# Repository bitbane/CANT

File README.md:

The CANT project is designed to allow people to screw around with CAN easily at layers 1/2.
All of the stuff that is normally handled by a CAN controller that is baked into sillicon is up for grabs.

CANT is designed to run on an ST Micro [Nucleo-H743ZI](http://www.st.com/en/evaluation-tools/nucleo-h743zi.html) 
(Update: The Nucleo-H743ZI has been discontinued. Its replacement the Nucleo-H743ZI2 works with CANT out of the box).
development board. This board was chosen due to its speed (400MHz) and essentially infinite ram and flash.

Note: If you have a MB1364C (and possibly D) revision of this board, the solder bridge at SB7 has to be soldered
closed to enable the GPIO pin. On revisions B and E this is controlled by the jumper JP6 which is in place by default.

## Getting started with the Nucleo-STM32H7 development board

The Nucleo-H743ZI board has an STLink V2.1 debugger built in, available via the Micro-USB port on the 
opposite side of the board from the RJ-45 jack. This port provides the serial port for communication, 
as well as the debugging interface. The serial port has a baud rate of 115200 kbps, 8N1. 

For CAN communication, PB12 is CAN RX and PB13 is CAN TX. Conveniently the CAN2 peripheral can also be 
multiplexed to these pins, so switching from normal CAN operation to CANT operation would be 
possible without rewiring. This is currently not implemented. I'm using the 
[TI SN65HVD232](http://www.ti.com/product/sn65hvd232?qgpn=sn65hvd232) 3.3V CAN transceiver, 
but any 3.3V CAN Transceiver should work. Some transceivers may require some additional 
programming or wiring, so check that if you go with something else.

If you are using the CANT shield, pin PA5 is used to toggle the analog switch that shorts CANH and CANL
together.

Additionally, GPIO pins PA4 and PA15 are configured as GPIO outputs. I find banging on these
useful during debugging. These pins, along with the two pins for the CAN peripheral, are all located
on connector CN7, on the upper-right of the dev board if the RJ-45 connector is pointed towards you.
STs documentation contains the schematics for this board, but connector CN7 is reproduced here for
convenience:

| PIN |     |     | PIN |
|:---:|:---:|:---:|:---:|
| PC6 | 1   | 2   | PB8 |
| PB15| 3   | 4   | PB9 |
| PB13| 5   | 6   | AVDD|
| PB12| 7   | 8   | GND |
| PA15| 9   | 10  | PA5 |
| PC7 | 11  | 12  | PA6 |
| PB5 | 13  | 14  |     |
| PB3 | 15  | 16  | PD14|
| PA4 | 17  | 18  | PD15|
| PB4 | 19  | 20  | PF12|

### Flashing pre-built CANT
The Nucleo-H743ZI dev board will present itself as a USB mass storage device. Dragging and dropping the CANT.bin file 
located in the `firmware/` folder to the dev board should properly flash the code to the dev board.

Alternatively, you will need openocd installed to flash the prebuilt CANT. At the time of this writing the latest version
of openocd (0.10.0) does not support the H743ZI, but it is supported in the openocd git repository.
Presumably support will be added in the next release of openocd. In order to flash the prebuilt CANT, type

```
make flash_prebuilt
```

### LEDs
The green LED (LED1) flashes at a rate of 1hz. The blue LED (LED2) changes state for every 128 CAN frames
that CANT has received. This is handy for ensuring that the CAN bus isn't dead and that CANT is properly
configured.

## Demos

Demo videos from my talks

Original Shmoocon Talk: 

Defcon 26 CHV Talk: 

## Developing with CANT

NOTE: Some older versions of the arm-none-eabi-gcc toolchain generate invalid opcodes with the optimizations that CANT uses. Specifically, the 4.9.3 version that ships with Ubuntu 16.04 tries to generate ARM instructions and switch to ARM mode, which the Cortex-M7 part does not support. If CANT just isn't working and you are winding up in the hardfault handler, this is likely the issue. Upgrade to a newer compiler version to fix this issue. The 7 series and newer seem to all work fine.

To start developing on CANT, all you need is an arm-none-eabi toolcahin installed and in your path.

## Shield

Version 0.1 of the shield was designed with a TI SN65HVD232DRG4 CAN transceiver, which costs about $1.75. Version 0.2 was redesigned for a TJA1051T/3 CAN transceiver which costs a little under a dollar. Version 0.2 also has an additional capacitor C6 for filtering the VIO line on the TJA1051T/3. Besides those changes, v0.1 and v0.2 are identical. Cost for building one is about $3.40 for one, or about $22.75 for 10, plus the cost of the PCB.

| Location | Part | Link | Notes |
|----------|------|------|-------|
| U1 | TJA1051T/3 CAN Transceiver | https://www.arrow.com/en/products/tja1051t3118/nxp-semiconductors |  |
| U2 | 74LVC1G66 Analog Switch | https://www.arrow.com/en/products/74lvc1g66gw125/nexperia |  |
| D1 | SP1002-02 Diode TVS Single Bi-Dir | https://www.arrow.com/en/products/sp1002-02jtg/littelfuse |  |
| R1 | 120 Ohm 0805 Resistor | https://www.arrow.com/en/products/nrc10j121trf/nic-components |  |
| C1, C4, C5 | 100pF 0805 Ceramic Capacitor | https://www.arrow.com/en/products/vj0805y101kxacw1bc/vishay |  |
| C2, C6 | 0.1uF 0805 Ceramic Capacitor  |  https://www.arrow.com/en/products/vj0805y104jxxcw1bc/vishay|  |
| C3 | 10uF 0805 Ceramic Capacitor | https://www.arrow.com/en/products/cl21a106kpfnnnf/samsung-electro-mechanics |  |
| J1 | 3.5mm Screw Terminal Block | https://www.arrow.com/en/products/ctb30512bk/camdenboss-ltd |  |
| CN7 | 20 pin 2.54mm pitch pin terminal | https://www.arrow.com/en/products/54102-t08-00/amphenol-fci | It's not clear, but these are sold singly. Buy 19 and they will come in a strip that you can use for CN7, CN8 and JP1 |
| CN8 | 16 pin 2.54mm pitch pin terminal |  |  |
| JP1 | 2 pin 2.54mm jumper header for 120Ohm resistor |  | Don't forget a jumper https://www.arrow.com/en/products/aksctgblack/assmann-wsw-components-inc |

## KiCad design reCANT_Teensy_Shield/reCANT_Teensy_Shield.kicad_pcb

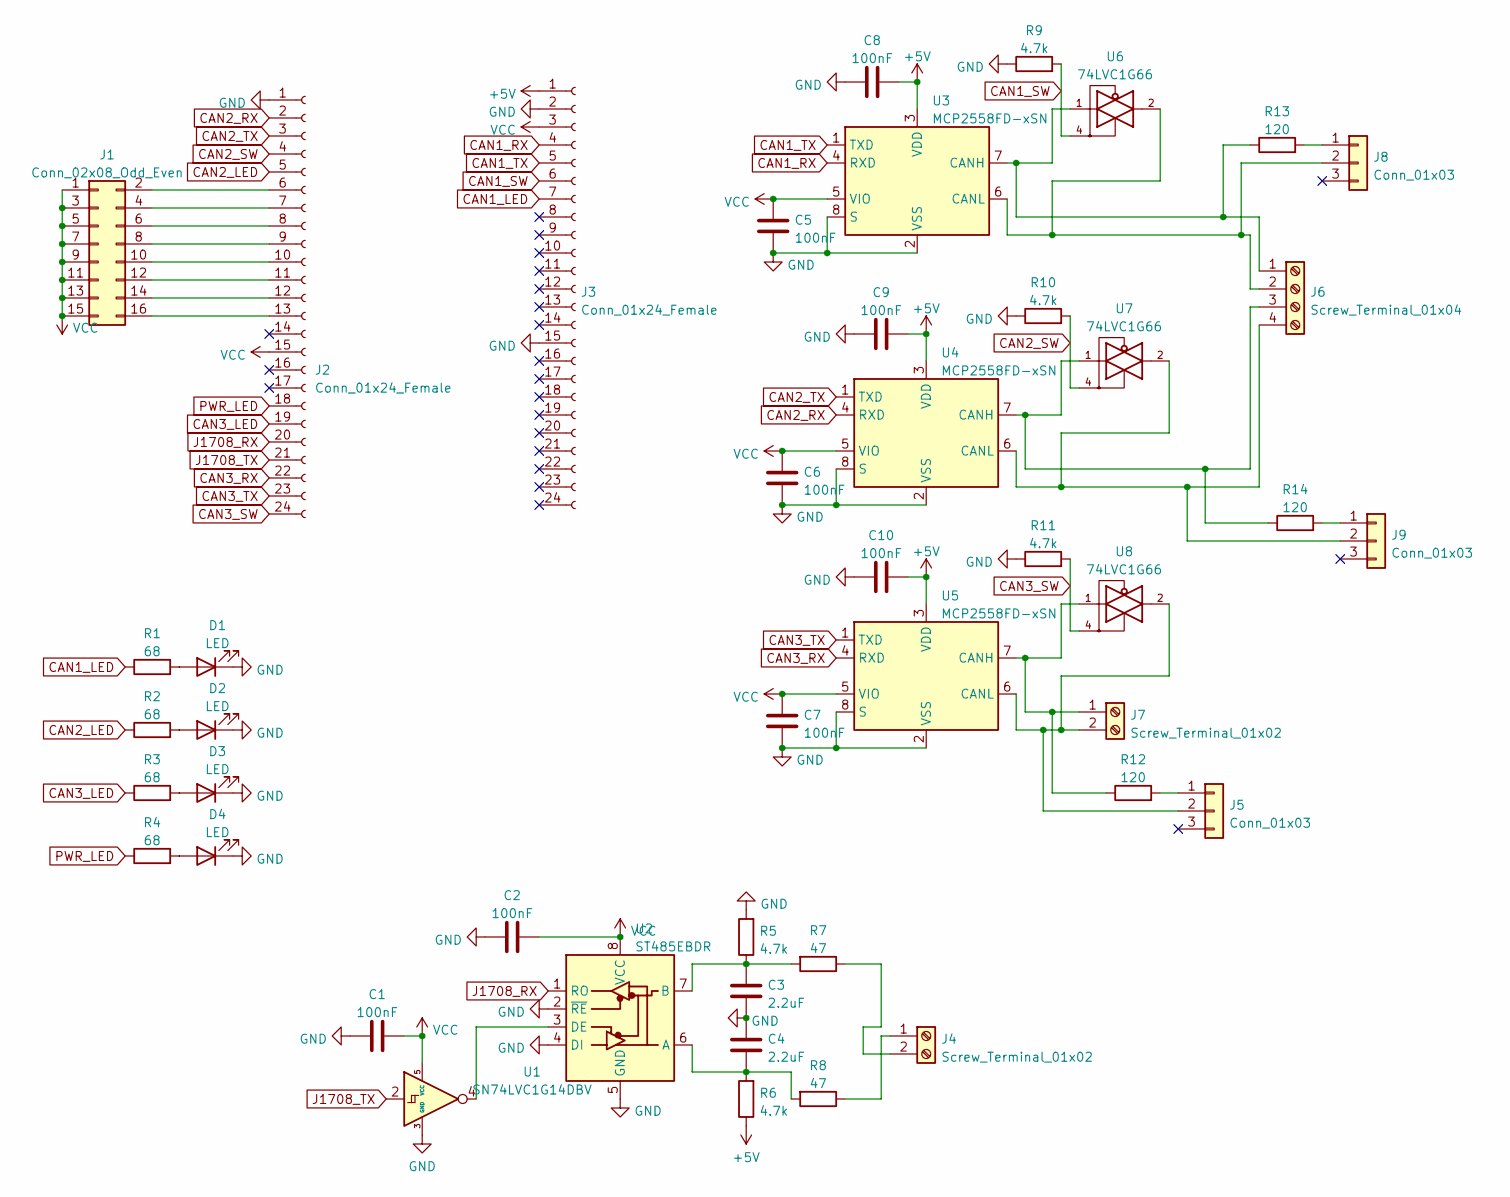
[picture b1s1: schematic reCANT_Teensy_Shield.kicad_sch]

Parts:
C1, C2, C5, C6, C7, C8, C9, C10: 100nF; C_0805_2012Metric
C3, C4: 2.2uF; C_0805_2012Metric
D1, D2, D3, D4: LED; LED_0805_2012Metric
J1: Conn_02x08_Odd_Even; PinHeader_2x08_P2.54mm_Vertical
J2, J3: Conn_01x24_Female; PinSocket_1x24_P2.54mm_Vertical
J4, J7: Screw_Terminal_01x02; TerminalBlock_Phoenix_PT-1,5-2-3.5-H_1x02_P3.50mm_Horizontal
J5, J8, J9: Conn_01x03; PinHeader_1x03_P2.54mm_Vertical
J6: Screw_Terminal_01x04; TerminalBlock_Phoenix_PT-1,5-4-3.5-H_1x04_P3.50mm_Horizontal
R1, R2, R3, R4: 68; R_0805_2012Metric
R5, R6, R9, R10, R11: 4.7k; R_0805_2012Metric
R7, R8: 47; R_0805_2012Metric
R12, R13, R14: 120; R_0805_2012Metric
U1: SN74LVC1G14DBV; SOT-23-5
U2: ST485EBDR; SOIC-8_3.9x4.9mm_P1.27mm
U3, U4, U5: MCP2558FD-xSN; SOIC-8_3.9x4.9mm_P1.27mm
U6, U7, U8: 74LVC1G66; SOT-353_SC-70-5_Handsoldering

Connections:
+5V: C8.2, C9.2, C10.2, J3.1, R6.1, U3.3 (VDD), U4.3 (VDD), U5.3 (VDD)
CAN1_LED: J3.7, R1.1
CAN1_RX: J3.4, U3.4 (RXD)
CAN1_SW: J3.6, R9.2, U6.4
CAN1_TX: J3.5, U3.1 (TXD)
CAN2_LED: J2.5, R2.1
CAN2_RX: J2.2, U4.4 (RXD)
CAN2_SW: J2.4, R10.2, U7.4
CAN2_TX: J2.3, U4.1 (TXD)
CAN3_LED: J2.19, R3.1
CAN3_RX: J2.22, U5.4 (RXD)
CAN3_SW: J2.24, R11.2, U8.4
CAN3_TX: J2.23, U5.1 (TXD)
GND: C1.2, C2.2, C3.2, C4.1, C5.1, C6.1, C7.1, C8.1, C9.1, C10.1, D1.1 (K), D2.1 (K), D3.1 (K), D4.1 (K), J2.1, J3.2, J3.15, R5.2, R9.1, R10.1, R11.1, U1.3 (GND), U2.2 (~RE), U2.4 (DI), U2.5 (GND), U3.2 (VSS), U3.8 (S), U4.2 (VSS), U4.8 (S), U5.2 (VSS), U5.8 (S), U6.3 (GND), U7.3 (GND), U8.3 (GND)
J1708_RX: J2.20, U2.1 (RO)
J1708_TX: J2.21, U1.2
unnamed: D1.2 (A), R1.2
unnamed: D2.2 (A), R2.2
unnamed: D3.2 (A), R3.2
unnamed: D4.2 (A), R4.2
unnamed: J1.2, J2.6
unnamed: J1.4, J2.7
unnamed: J1.6, J2.8
unnamed: J1.8, J2.9
unnamed: J1.10, J2.10
unnamed: J1.12, J2.11
unnamed: J1.14, J2.12
unnamed: J1.16, J2.13
unnamed: J4.1, R8.1
unnamed: J4.2, R7.1
unnamed: J5.1, R12.2
unnamed: J7.1, R12.1, U5.7 (CANH), U8.1
unnamed: J5.2, J7.2, U5.6 (CANL), U8.2
unnamed: J8.1, R13.2
unnamed: J9.1, R14.2
unnamed: U1.4, U2.3 (DE)
unnamed: C4.2, R6.2, R8.2, U2.6 (A)
unnamed: C3.1, R5.1, R7.2, U2.7 (B)
unnamed: J6.2, J8.2, U3.6 (CANL), U6.2
unnamed: J6.1, R13.1, U3.7 (CANH), U6.1
unnamed: J6.4, J9.2, U4.6 (CANL), U7.2
unnamed: J6.3, R14.1, U4.7 (CANH), U7.1
PWR_LED: J2.18, R4.1
VCC: C1.1, C2.1, C5.2, C6.2, C7.2, J1.1, J1.3, J1.5, J1.7, J1.9, J1.11, J1.13, J1.15, J2.15, J3.3, U1.5 (VCC), U2.8 (VCC), U3.5 (VIO), U4.5 (VIO), U5.5 (VIO), U6.5 (VCC), U7.5 (VCC), U8.5 (VCC)

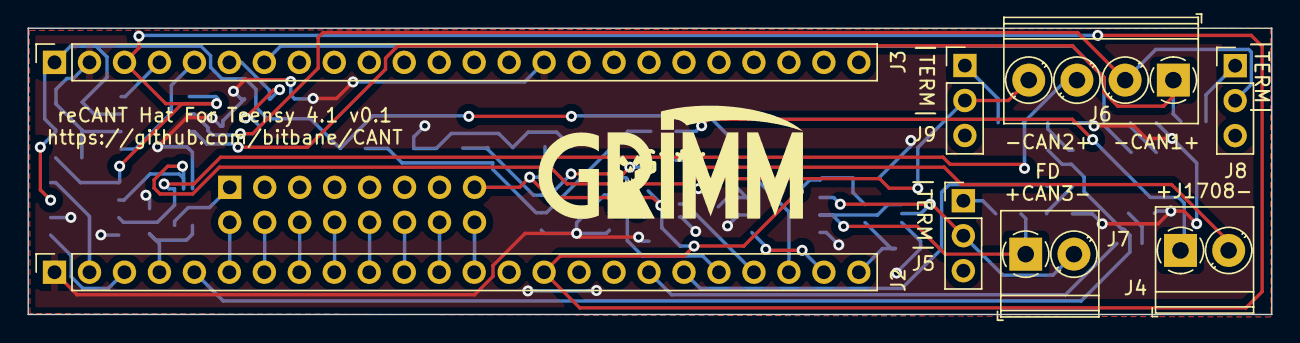
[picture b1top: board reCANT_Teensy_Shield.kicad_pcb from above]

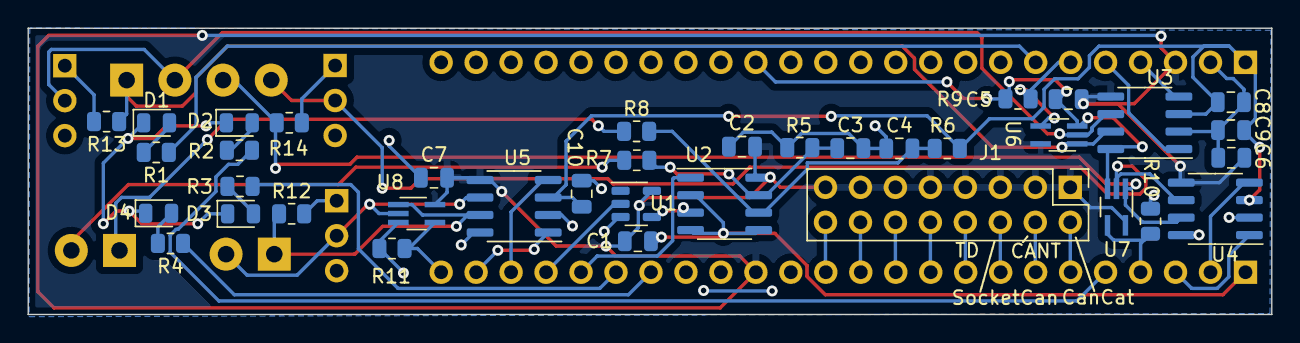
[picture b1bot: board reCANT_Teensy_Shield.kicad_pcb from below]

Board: 2 copper layers, 90.3 x 20.8 mm, 45 parts (37 on the bottom side), 44 nets.

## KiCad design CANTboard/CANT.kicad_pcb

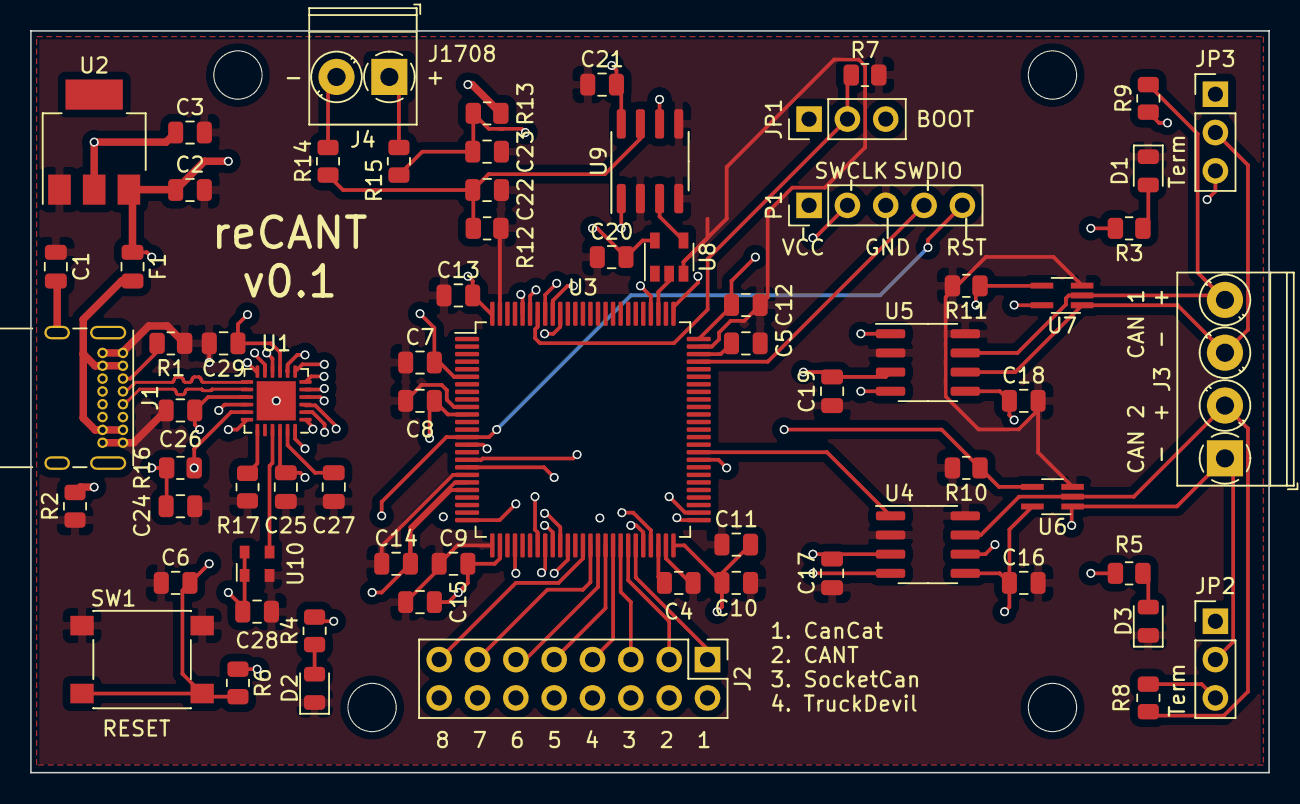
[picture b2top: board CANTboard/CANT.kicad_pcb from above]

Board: 4 copper layers, 82.0 x 49.1 mm, 73 parts (0 on the bottom side), 65 nets.

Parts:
 : MountingHole_3.2mm_M3
 #2,  #3,  #4: MountingHole_3.2mm_M3
C1, C15, C26, C27: 1uF; C_0805_2012Metric
C2, C6, C7, C8, C9, C10, C12, C13, C14, C16, C17, C18, C19, C20, C21, C25, C28, C29: 100nF; C_0805_2012Metric
C3: 10uF; C_0805_2012Metric
C4, C5, C22, C23: 2.2uF; C_0805_2012Metric
C11, C24: 4.7uF; C_0805_2012Metric
D1, D3: LED-RED; LED_0805_2012Metric
D2: LED-GREEN; LED_0805_2012Metric
F1: Polyfuse; C_0805_2012Metric
J1: USB_C_Receptacle_USB2.0; USB_C_Receptacle_GCT_USB4085
J2: Conn_02x08_Odd_Even; PinHeader_2x08_P2.54mm_Vertical
J3: Screw_Terminal_01x04; TerminalBlock_Phoenix_PT-1,5-4-3.5-H_1x04_P3.50mm_Horizontal
J4: Screw_Terminal_01x02; TerminalBlock_Phoenix_PT-1,5-2-3.5-H_1x02_P3.50mm_Horizontal
JP1, JP2, JP3: Jumper_NC_Dual; PinHeader_1x03_P2.54mm_Vertical
P1: SWD; PinHeader_1x05_P2.54mm_Vertical
R1, R2: 5.1K; R_0805_2012Metric
R3, R4, R5: 68; R_0805_2012Metric
R6: 100K; R_0805_2012Metric
R7: 10k; R_0805_2012Metric
R8, R9: 120; R_0805_2012Metric
R10, R11, R12, R13: 4.7K; R_0805_2012Metric
R14, R15: 47; R_0805_2012Metric
R16: 20K; R_0805_2012Metric
R17: 8.06K; R_0805_2012Metric
SW1: SW_SPST; SW_SPST_PTS645
U1: USB3343; QFN-24-1EP_4x4mm_P0.5mm_EP2.6x2.6mm
U2: LD1117S33TR; SOT-223
U3: STM32H743VITx; LQFP-100_14x14mm_P0.5mm
U4, U5: MCP2558FD-xSN; SOIC-8_3.9x4.9mm_P1.27mm
U6, U7: 74LVC1G66; SOT-353_SC-70-5_Handsoldering
U8: SN74LVC1G14DBV; SOT-23-5
U9: ST485EBDR; SOIC-8_3.9x4.9mm_P1.27mm
U10: DSC1001; Oscillator_SMD_Microchip_DSC1001-4Pin_2.5x2.0mm

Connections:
/HS_USB/D+: J1.A6, J1.B6, U1.13
/HS_USB/D-: J1.A7, J1.B7, U1.14
/Microcontroller/NRST: C6.2, P1.5, R6.2, SW1.2, U3.14
BOOT0: JP1.2, R7.1, U3.94
CAN1_H: J3.4, R9.2, U5.7, U7.2
CAN1_L: J3.3, JP3.2, U5.6, U7.1
CAN1_RX: U3.95, U5.4
CAN1_SHORT: R11.1, U3.93, U7.4
CAN1_TX: U3.96, U5.1
CAN3_H: J3.2, R8.2, U4.7, U6.2
CAN3_L: J3.1, JP2.2, U4.6, U6.1
CAN3_RX: U3.59, U4.4
CAN3_SHORT: R10.1, U3.92, U6.4
CAN3_TX: U3.60, U4.1
GND: C1.1, C2.2, C3.2, C4.2, C5.2, C6.1, C7.1, C8.1, C9.1, C10.1, C11.1, C12.1, C13.1, C14.1, C15.1, C16.2, C17.1, C18.2, C19.1, C20.1, C21.1, C22.2, C23.1, C24.1, C25.1, C26.2, C27.1, C28.2, C29.2, D1.1, D2.1, D3.1, J1.A1, J1.A12, J1.B1, J1.B12, P1.3, R1.1, R2.1, R7.2, R10.2, R11.2, R12.2, R17.2, SW1.1, U1.25, U2.1, U3.10, U3.19, U3.26, U3.49, U3.74, U3.99, U4.2, U4.8, U5.2, U5.8, U6.3, U7.3, U8.3, U9.2, U9.4, U9.5, U10.2
J1708_RX: U3.79, U9.1
J1708_TX: U3.78, U8.2
LED_ACT1: R3.2, U3.32
LED_ACT2: R5.2, U3.33
LED_PWR1: R4.2, U3.36
unnamed: C1.2, J1.S1
unnamed: C4.1, U3.48
unnamed: C5.1, U3.73
unnamed: C22.1, R12.1, R14.1, U9.7
unnamed: C23.2, R13.2, R15.1, U9.6
unnamed: C27.2, U1.23
unnamed: D1.2, R3.1
unnamed: D2.2, R4.1
unnamed: D3.2, R5.1
unnamed: F1.2, J1.A4, J1.A9, J1.B4, J1.B9
unnamed: J1.A5, R1.2
unnamed: J1.B5, R2.2
unnamed: J2.1, U3.45
unnamed: J2.3, U3.44
unnamed: J2.5, U3.43
unnamed: J2.7, U3.42
unnamed: J2.9, U3.41
unnamed: J2.11, U3.40
unnamed: J2.13, U3.39
unnamed: J2.15, U3.38
unnamed: J4.1, R15.2
unnamed: J4.2, R14.2
unnamed: JP2.3, R8.1
unnamed: JP3.3, R9.1
unnamed: R16.1, U1.17
unnamed: R17.1, U1.19
unnamed: U1.21, U10.3
unnamed: U8.4, U9.3
SWCLK: P1.2, U3.76
SWDIO: P1.4, U3.72
USB_CK: U1.2, U3.29
USB_D0: U1.4, U3.25
USB_D1: U1.5, U3.34
USB_D2: U1.6, U3.35
USB_D3: U1.7, U3.46
USB_D4: U1.8, U3.47
USB_D5: U1.10, U3.51
USB_D6: U1.11, U3.52
USB_D7: U1.12, U3.91
USB_DIR: U1.1, U3.17
USB_NXT: U1.3, U3.18
USB_STP: U1.24, U3.15
VBUS: C2.1, C17.2, C19.2, C24.2, F1.1, R13.1, R16.2, U2.3, U4.3, U5.3
VCC: C3.1, C7.2, C8.2, C9.2, C10.2, C11.2, C12.2, C13.2, C14.2, C15.2, C16.1, C18.1, C20.2, C21.2, C25.2, C28.1, C29.1, J2.2, J2.4, J2.6, J2.8, J2.10, J2.12, J2.14, J2.16, JP1.3, P1.1, R6.1, U1.9, U1.16, U1.22, U2.2, U3.6, U3.11, U3.20, U3.21, U3.27, U3.50, U3.75, U3.100, U4.5, U5.5, U6.5, U7.5, U8.5, U9.8, U10.1, U10.4
VDD33: C26.1, U1.15, U1.18

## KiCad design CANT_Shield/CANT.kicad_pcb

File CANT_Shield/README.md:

The CANT project is designed to allow people to screw around with CAN easily at layers 1/2.
All of the stuff that is normally handled by a CAN controller that is baked into sillicon is up for grabs.

THis CANT shield hardware is designed to run on an ST Micro
[Nucleo-H743ZI](http://www.st.com/en/evaluation-tools/nucleo-h743zi.html)
development board. This board was chosen due to its speed (400MHz) and
essentially infinite ram and flash.

## Getting started with the Nucleo-STM32H7 development board

The Nucleo-H743ZI board has an STLink V2.1 debugger built in, available via the Micro-USB port on the 
opposite side of the board from the RJ-45 jack. This port provides the serial port for communication, 
as well as the debugging interface. The serial port has a baud rate of 115200 kbps, 8N1. 

For CAN communication, PB12 is CAN RX and PB13 is CAN TX. Conveniently the CAN2 peripheral can also be 
multiplexed to these pins, so switching from normal CAN operation to CANT operation would be 
possible without rewiring. This is currently not implemented. I'm using the 
[TI SN65HVD232](http://www.ti.com/product/sn65hvd232?qgpn=sn65hvd232) 3.3V CAN transceiver, 
but any 3.3V CAN Transceiver should work. Some transceivers may require some additional 
programming or wiring, so check that if you go with something else.

If you are using the CANT shield, pin PA5 is used to toggle the analog switch that shorts CANH and CANL
together.

Additionally, GPIO pins PA4 and PA15 are configured as GPIO outputs. I find banging on these
useful during debugging. These pins, along with the two pins for the CAN peripheral, are all located
on connector CN7, on the upper-right of the dev board if the RJ-45 connector is pointed towards you.
STs documentation contains the schematics for this board, but connector CN7 is reproduced here for
convenience:

| PIN |     |     | PIN |
|:---:|:---:|:---:|:---:|
| PC6 | 1   | 2   | PB8 |
| PB15| 3   | 4   | PB9 |
| PB13| 5   | 6   | AVDD|
| PB12| 7   | 8   | GND |
| PA15| 9   | 10  | PA5 |
| PC7 | 11  | 12  | PA6 |
| PB5 | 13  | 14  |     |
| PB3 | 15  | 16  | PD14|
| PA4 | 17  | 18  | PD15|
| PB4 | 19  | 20  | PF12|

### Flashing pre-built CANT
The Nucleo-H743ZI dev board will present itself as a USB mass storage device. Dragging and dropping the CANT.bin file 
located in the `firmware/` folder to the dev board should properly flash the code to the dev board.

Alternatively, you will need openocd installed to flash the prebuilt CANT. At the time of this writing the latest version
of openocd (0.10.0) does not support the H743ZI, but it is supported in the openocd git repository.
Presumably support will be added in the next release of openocd. In order to flash the prebuilt CANT, type

```
make flash_prebuilt
```

### LEDs
The green LED (LED1) flashes at a rate of 1hz. The blue LED (LED2) changes state for every 128 CAN frames
that CANT has received. This is handy for ensuring that the CAN bus isn't dead and that CANT is properly
configured.

## Shield

Version 0.1 of the shield was designed with a TI SN65HVD232DRG4 CAN transceiver, which costs about $1.75. Version 0.2 was redesigned for a TJA1051T/3 CAN transceiver which costs a little under a dollar. Version 0.2 also has an additional capacitor C6 for filtering the VIO line on the TJA1051T/3. Besides those changes, v0.1 and v0.2 are identical. Cost for building one is about $3.40 for one, or about $22.75 for 10, plus the cost of the PCB.

| Location | Part | Link | Notes |
|----------|------|------|-------|
| U1 | TJA1051T/3 CAN Transceiver | https://www.arrow.com/en/products/tja1051t3118/nxp-semiconductors |  |
| U2 | 74LVC1G66 Analog Switch | https://www.arrow.com/en/products/74lvc1g66gw125/nexperia |  |
| D1 | SP1002-02 Diode TVS Single Bi-Dir | https://www.arrow.com/en/products/sp1002-02jtg/littelfuse |  |
| R1 | 120 Ohm 0805 Resistor | https://www.arrow.com/en/products/nrc10j121trf/nic-components |  |
| C1, C4, C5 | 100pF 0805 Ceramic Capacitor | https://www.arrow.com/en/products/vj0805y101kxacw1bc/vishay |  |
| C2, C6 | 0.1uF 0805 Ceramic Capacitor  |  https://www.arrow.com/en/products/vj0805y104jxxcw1bc/vishay|  |
| C3 | 10uF 0805 Ceramic Capacitor | https://www.arrow.com/en/products/cl21a106kpfnnnf/samsung-electro-mechanics |  |
| J1 | 3.5mm Screw Terminal Block | https://www.arrow.com/en/products/ctb30512bk/camdenboss-ltd |  |
| CN7 | 20 pin 2.54mm pitch pin terminal | https://www.arrow.com/en/products/54102-t08-00/amphenol-fci | It's not clear, but these are sold singly. Buy 19 and they will come in a strip that you can use for CN7, CN8 and JP1 |
| CN8 | 16 pin 2.54mm pitch pin terminal |  |  |
| JP1 | 2 pin 2.54mm jumper header for 120Ohm resistor |  | Don't forget a jumper https://www.arrow.com/en/products/aksctgblack/assmann-wsw-components-inc |

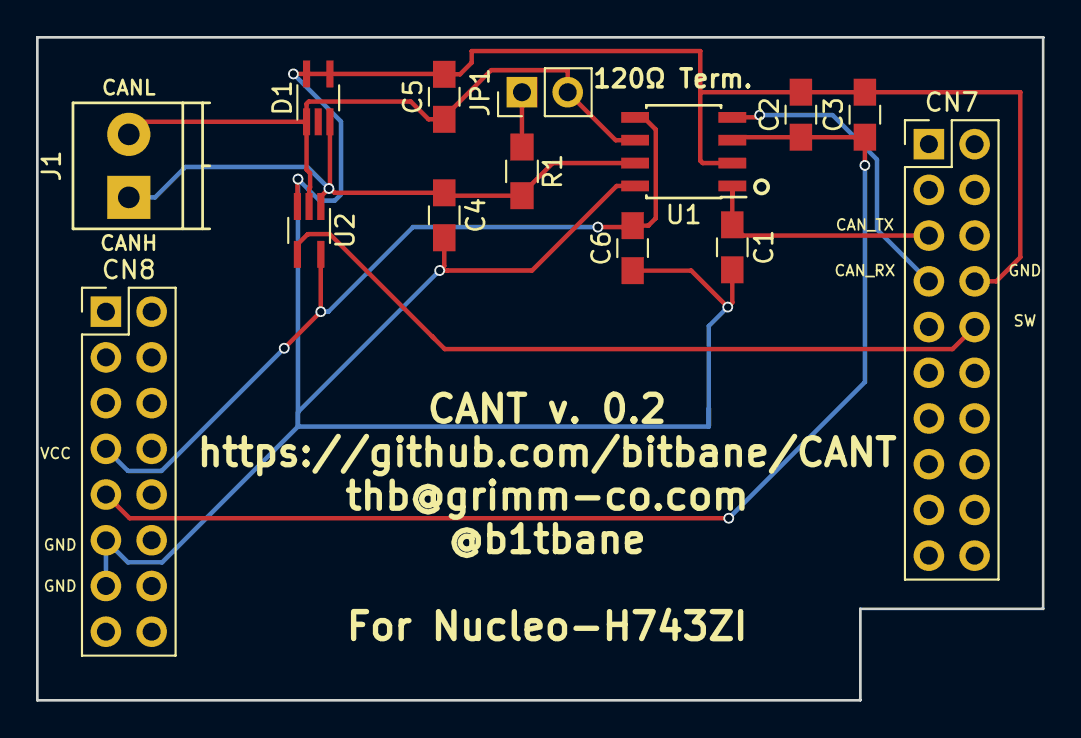
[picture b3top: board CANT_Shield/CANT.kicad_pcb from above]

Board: 2 copper layers, 55.9 x 36.8 mm, 14 parts (0 on the bottom side), 9 nets.

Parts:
C1, C4, C5: 100pF; C_0805_HandSoldering
C2, C6: 0.1uF; C_0805_HandSoldering
C3: 10 uF; C_0805_HandSoldering
CN7: CN7; Pin_Header_Straight_2x10_Pitch2.54mm
CN8: CN8; Pin_Header_Straight_2x08_Pitch2.54mm
D1: SP1002-02; SOT-353_SC-70-5_Handsoldering
J1: Screw_Terminal_01x02; TerminalBlock_Pheonix_PT-3.5mm_2pol
JP1: Jumper; Pin_Header_Straight_1x02_Pitch2.54mm
R1: 120; R_0805_HandSoldering
U1: TJA1051T_3; SOIC-8_3.9x4.9mm_Pitch1.27mm
U2: 74LVC1G66; SOT-353_SC-70-5_Handsoldering

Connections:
5V: C2.1, C3.1, CN8.9, U1.3
CAN_RX: CN7.7, U1.4
CAN_TX: C1.1, CN7.5, U1.1
GND: C1.2, C2.2, C3.2, C4.2, C5.2, C6.1, CN7.8, CN8.11, CN8.13, D1.4, D1.5, U1.2, U1.8, U2.3
unnamed: C4.1, D1.3, J1.1, R1.2, U1.7, U2.1
unnamed: C5.1, D1.1, J1.2, JP1.2, U1.6, U2.2
unnamed: CN7.10, U2.4
unnamed: JP1.1, R1.1
VCC: C6.2, CN8.7, U1.5, U2.5

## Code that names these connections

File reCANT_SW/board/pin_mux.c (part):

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processor_version: 12.0.0
external_user_signals: {}
pin_labels:
- {pin_num: F2, pin_signal: GPIO_EMC_04, label: CAN2_SW, identifier: CAN2_SW}
- {pin_num: G5, pin_signal: GPIO_EMC_05, label: CAN2_LED, identifier: CAN2_LED}
- {pin_num: H5, pin_signal: GPIO_EMC_06, label: RUN_CANCAT, identifier: RUN_CANCAT}
- {pin_num: H3, pin_signal: GPIO_EMC_08, label: RUN_CANT, identifier: RUN_CANT}
- {pin_num: D9, pin_signal: GPIO_B0_10, label: RUN_SOCKETCAN, identifier: RUN_SOCKETCAN}
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- {pin_num: A10, pin_signal: GPIO_B0_11, label: RUN_SW6, identifier: RUN_SW6}
- {pin_num: D7, pin_signal: GPIO_B0_00, label: RUN_SW7, identifier: RUN_SW7}
- {pin_num: E8, pin_signal: GPIO_B0_02, label: RUN_SW8, identifier: RUN_SW8}
- {pin_num: C10, pin_signal: GPIO_B0_12, label: CAN3_SW, identifier: CAN3_SW}
- {pin_num: J13, pin_signal: GPIO_AD_B1_11, label: CAN1_SW, identifier: CAN1_SW}
- {pin_num: L13, pin_signal: GPIO_AD_B1_10, label: CAN1_LED, identifier: CAN1_LED}
- {pin_num: D8, pin_signal: GPIO_B0_03, label: TEENSY_LED, identifier: TEENSY_LED}
- {pin_num: G12, pin_signal: GPIO_AD_B1_14, label: PWR_LED, identifier: PWR_LED}
- {pin_num: J14, pin_signal: GPIO_AD_B1_15, label: CAN3_LED, identifier: CAN3_LED}
 * BE CAREFUL MODIFYING THIS COMMENT - IT IS YAML SETTINGS FOR TOOLS ***********
 */

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void BOARD_InitPins(void) {
  CLOCK_EnableClock(kCLOCK_Iomuxc);           

  /* GPIO configuration of CAN1_LED on GPIO_AD_B1_10 (pin L13) */
  gpio_pin_config_t CAN1_LED_config = {
      .direction = kGPIO_DigitalOutput,
      .outputLogic = 0U,
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  /* Initialize GPIO functionality on GPIO_AD_B1_10 (pin L13) */
  GPIO_PinInit(GPIO1, 26U, &CAN1_LED_config);

  /* GPIO configuration of CAN1_SW on GPIO_AD_B1_11 (pin J13) */
  gpio_pin_config_t CAN1_SW_config = {
      .direction = kGPIO_DigitalOutput,
      .outputLogic = 0U,
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  /* Initialize GPIO functionality on GPIO_AD_B1_11 (pin J13) */
  GPIO_PinInit(GPIO1, 27U, &CAN1_SW_config);

  /* GPIO configuration of PWR_LED on GPIO_AD_B1_14 (pin G12) */
  gpio_pin_config_t PWR_LED_config = {
      .direction = kGPIO_DigitalOutput,
      .outputLogic = 0U,
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  /* Initialize GPIO functionality on GPIO_AD_B1_14 (pin G12) */
  GPIO_PinInit(GPIO1, 30U, &PWR_LED_config);

  /* GPIO configuration of CAN3_LED on GPIO_AD_B1_15 (pin J14) */
  gpio_pin_config_t CAN3_LED_config = {
      .direction = kGPIO_DigitalOutput,
      .outputLogic = 0U,
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  /* Enable GPIO pin interrupt on GPIO_B0_11 (pin A10) */
  GPIO_PortEnableInterrupts(GPIO2, 1U << 11U);

  /* GPIO configuration of CAN3_SW on GPIO_B0_12 (pin C10) */
  gpio_pin_config_t CAN3_SW_config = {
      .direction = kGPIO_DigitalOutput,
      .outputLogic = 0U,
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  /* Enable GPIO pin interrupt on GPIO_B1_01 (pin B11) */
  GPIO_PortEnableInterrupts(GPIO2, 1U << 17U);

  /* GPIO configuration of CAN2_SW on GPIO_EMC_04 (pin F2) */
  gpio_pin_config_t CAN2_SW_config = {
      .direction = kGPIO_DigitalOutput,
      .outputLogic = 0U,
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  /* Initialize GPIO functionality on GPIO_EMC_04 (pin F2) */
  GPIO_PinInit(GPIO4, 4U, &CAN2_SW_config);

  /* GPIO configuration of CAN2_LED on GPIO_EMC_05 (pin G5) */
  gpio_pin_config_t CAN2_LED_config = {
      .direction = kGPIO_DigitalOutput,
      .outputLogic = 0U,
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
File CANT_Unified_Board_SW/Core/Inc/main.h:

/* USER CODE BEGIN Header */
/**
  ******************************************************************************
  * @file           : main.h
  * @brief          : Header for main.c file.
  *                   This file contains the common defines of the application.
  ******************************************************************************
  * @attention
  *
  * <h2><center>&copy; Copyright (c) 2021 STMicroelectronics.
  * All rights reserved.</center></h2>
  *
  * This software component is licensed by ST under Ultimate Liberty license
  * SLA0044, the "License"; You may not use this file except in compliance with
  * the License. You may obtain a copy of the License at:
  *                             www.st.com/SLA0044
  *
  ******************************************************************************
  */
/* USER CODE END Header */

/* Define to prevent recursive inclusion -------------------------------------*/
#ifndef __MAIN_H
#define __MAIN_H

#ifdef __cplusplus
extern "C" {
#endif

/* Includes ------------------------------------------------------------------*/
#include "stm32h7xx_hal.h"

/* Private includes ----------------------------------------------------------*/
/* USER CODE BEGIN Includes */

/* USER CODE END Includes */

/* Exported types ------------------------------------------------------------*/
/* USER CODE BEGIN ET */

/* USER CODE END ET */

/* Exported constants --------------------------------------------------------*/
/* USER CODE BEGIN EC */

/* USER CODE END EC */

/* Exported macro ------------------------------------------------------------*/
/* USER CODE BEGIN EM */

/* USER CODE END EM */

/* Exported functions prototypes ---------------------------------------------*/
void Error_Handler(void);

/* USER CODE BEGIN EFP */

/* USER CODE END EFP */

/* Private defines -----------------------------------------------------------*/
#define LED_ACT1_Pin GPIO_PIN_4
#define LED_ACT1_GPIO_Port GPIOC
#define LED_ACT2_Pin GPIO_PIN_5
#define LED_ACT2_GPIO_Port GPIOC
#define LED_PWR_Pin GPIO_PIN_2
#define LED_PWR_GPIO_Port GPIOB
#define MODE8_Pin GPIO_PIN_8
#define MODE8_GPIO_Port GPIOE
#define MODE7_Pin GPIO_PIN_9
#define MODE7_GPIO_Port GPIOE
#define MODE6_Pin GPIO_PIN_10
#define MODE6_GPIO_Port GPIOE
#define MODE5_Pin GPIO_PIN_11
#define MODE5_GPIO_Port GPIOE
#define MODE4_Pin GPIO_PIN_12
#define MODE4_GPIO_Port GPIOE
#define MODE3_Pin GPIO_PIN_13
#define MODE3_GPIO_Port GPIOE
#define MODE2_Pin GPIO_PIN_14
#define MODE2_GPIO_Port GPIOE
#define MODE1_Pin GPIO_PIN_15
#define MODE1_GPIO_Port GPIOE
#define CAN3_SHORT_Pin GPIO_PIN_6
#define CAN3_SHORT_GPIO_Port GPIOB
#define CAN1_SHORT_Pin GPIO_PIN_7
#define CAN1_SHORT_GPIO_Port GPIOB
/* USER CODE BEGIN Private defines */

/* USER CODE END Private defines */

#ifdef __cplusplus
}
#endif

#endif /* __MAIN_H */

/************************ (C) COPYRIGHT STMicroelectronics *****END OF FILE****/

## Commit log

2017-10-05 Adding readme
2017-10-05 Starting out with instructions for getting the FRDM-KL43z running
2017-10-05 Added start of development instructions to Readme
2017-10-06 Switched from the FRDM-KL43Z to the STM32F4-Discovery board
2017-10-06 CAN sniffing is working, though needs some tweaking at low speeds
2017-10-06 Moved the ARBID printf out of the interrupt and added a CAN polling function to check if a new message has been received.
2017-10-29 Starting the process of archiving the STM32F4 work and starting dev on the STM32H7
2017-10-30 Got it compiling for STM32H7
2017-12-18 Added scripts for debugging and flashing
2017-12-20 Serial working on debug
2017-12-20 Missed some files from previous commit
2017-12-20 CAN and menu stuff imported from STM32F4 project. Menu seems to work, CAN is currently untested
2017-12-22 Fix up timer and GPIO pin in CAN driver
2018-01-01 Getting CAN working. The GPIO input interrupt fires immediately when enabled, even if cleared, which is dumb, but a fix is in for that. This commit disables serial for testing purposes
2018-01-01 Re-enabled menus. Still getting an occasional hardfault, but things are actually working
2018-01-02 Implement setting the arbid (currently only one supported) and clean up menu support so that it works more gracefully
2018-01-02 Enable CAN output
2018-01-03 Fixed interrupt issue on GPIO better. Hardfault not such an issue now?
2018-01-03 Added functionality to write an int to the serial port without using printf
2018-01-08 Count CAN messages with the LED instead of printing them
2018-01-08 Make Makefile create its own directories
2018-01-09 Changing -Ofast to -Os to fix hardfault (it appears that the latest arm toolchain works with -Ofast, but -Os does not seem to be any slower so sticking with the change). No longer printing CAN messag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
2018-01-09 At this point I've gleaned as much from the stm32f4 code that I don't need it anymore
2018-01-09 Fix merge issue
2018-01-09 Menu no longer drops characters. Simplified __io_putchar to not use the HAL
2018-01-09 Fixing the initial delay bug, ensure sampling occurs in the middle of a bit
2018-01-09 Adding timer3 which triggers on CAN edges
2018-01-11 Fixed a couple minor bugs in the CAN parsing, added the first attack, a simple bus killer that always transmits an arbitration ID of 0
2018-01-11 Increase efficiency for disabling the GPIO interrupt, it wasn't happening fast enough on a busy bus
2018-01-12 Fix CAN bit stuffing on receive
2018-01-13 Adding some helper functions for creating CAN bitstreams
2018-01-13 Added a data replacer attack. Also added functions to read numbers from the user and refactored the current data reading code
2018-01-15 Adding overload frame attack and fix up how Timer 3 is handled to fix spurious timing issue
2018-01-15 Fix up error frame handling, which caused the data replacement attack to work
2018-01-15 Fix up overload frame transmission
2018-01-15 Updating readme and adding prebuilt firmware
2018-01-16 Add license
2018-01-16 Updating gitignore
2018-01-17 Add section on the LEDs to the readme
2018-02-11 Adding first iteration of CANT shield. No power supply, no shorting
2018-07-15 Version 0.1 of shield, with analog switch
2018-07-16 Added board name to silkscreen
2018-07-16 Changed to rev 0.2, switched to using TJA1051 CAN transceiver
2018-07-23 Finished with rev 0.2 of the CANT shield, mostly a redesign for the much cheaper TJA1051T/3
2018-07-23 Adding instructions for building the shield
2018-07-29 The forcing recessive functionality is not working, but NACK and Cyber Paperclip mode are
2018-07-29 Fixed bug in can.c, I was masking off the lower 3 bits instead of the lower bit when transmitting data replacer data. Fixed up scripts to explicitly require python 2
2018-07-29 Updating readme to mention PA5's new usage
2018-07-29 Generating new prebuilt CANT.elf
2018-07-31 Properly fix bug in data replacer that I fixed improperly in the last commit
2018-08-08 Partially working, need to update all prompts and figure out how to actually clear text from the console
2018-08-08 Backspace now works
2018-08-08 Accidentally nuked the firmware folder
2018-08-09 Can now uninstall attacks. Also automatically generates the prebuilt file
2018-08-12 Fix README formatting
2018-08-14 Updating readme
2018-09-10 Add note to watch out for old compiler versions
2018-10-03 Update instructions to properly flash dev board. Closes #2
2018-11-08 Update README.md
    Add links to demo and talk videos
2018-11-08 Update README.md
    Formatting change
2019-01-07 Fix a silly typo in uart menu
2019-02-12 insignificant change to PCB
2019-02-12 Initial checkin of new CANT board
2019-05-15 Laid out CANT board based on STM32H7
2019-05-16 Added logo, because how could I forget that
2019-05-31 Fix VCAP connection issue - apparently, these are not supposed to be connected to VDD
2019-10-09 Update readme to indicate that the replacement dev board works. Closes #4
2019-10-09 Fix README typo
2020-10-31 Starting design of unified board
2020-11-04 Finished layout, ordered first set of prototype boards
2020-11-04 Mark pin 1 of all ICs
2021-03-03 Add option to Makefile to build with newer GCC
2021-03-03 Update Makefile with option to build on newer GCC, add readme to CANT_Shield
2021-07-30 Switched to USB-C, in process of switching to USB-HS
2021-08-02 Re-design for 480mbps USB-C. Schematic split into multiple sheets, connections made, ERC passes, footprints assigned.
2021-08-02 Everything routed, commiting before last check before ordering PCBs
2021-08-03 Final review, ordering v0.1 PCB off this design
2021-08-13 Renaming schematics and hardware folder
2021-08-13 Add LCSC part numbers for each component. Not that chipocalypse makes building this right now feasible...
2021-08-16 Fixed USB differential pair routing to have correct impedence
2021-08-17 Adjusted USB trace spacing to 5 mil from 3.5 mil. JLCPCB can do 3.5 mil, but 5 mil is the minimum a lot of other places.
2021-08-17 Reorganization in prep for starting to write code. Updated readmes
2021-08-17 Fix minor typos and add assembly note to README
2021-08-19 Generated first round of code
2022-03-15 Added test points for debugging USB. Fixed impedence on USB traces to be correct for JLCPCBs JLC7628 buildup
2022-06-28 Adding option to make debug build from the commandline
2022-06-28 Add option to sniff and print CAN traffic, mostly as a debug/hardware check feature.
2022-07-13 Creating shield for Teensy 4.1. Design schematic done and traces routed on PCB. Still need to move silkscreens around.
2022-07-13 Git silkscreen set
2022-07-13 Added version number
2022-07-20 Initial board pin configuration
2022-07-20 Base project compiles
2022-07-20 Fixing warnings
2022-07-20 Adding gitignore
2022-07-20 Removing accidentally commited build files
2022-07-21 Trying to add USB CDC support, thinking of starting with a USB CDC example project first
2022-07-21 Still working on USB CDC
2022-07-21 Linking, has IVT in the right place, not running
2022-07-21 Missed a couple files that should have been in the first commit
2022-07-22 Regenerated without USB (Switching to TeensyUSB)
2022-07-22 Building and linking with correct(?) startup and linker script
2022-07-22 Flash image looks right but something is still wrong
2022-07-23 Works as long as main does not call BOARD_InitBootPeripherals
2022-07-23 CAN initalization was hanging, not sure why. Removed CAN peripherals from the configuration since I need to configure them on a per-connection basis anyhow
2022-07-23 Commiting prior to attempting to incorporate TinyUSB
2022-07-23 Basic functionality is working with USB Serial, basic console functionality, and the first attempt at a test suite
2022-07-23 Added flash target to Makefile
2022-07-25 Change the number of flashes based on the selected program
2022-07-26 Verfied remuxing TX pins as GPIO is working. Test application is fully functional besides testing CAN and J1708 RX Functionality
2022-07-26 Update README.md
    Add note to README about specific board revisions.
2022-07-27 Starting to bring CANT in
2022-07-27 CANT code compiling, untested
2022-07-28 Menu works, CANT hangs on initialization
2022-07-28 Printf does work.
2022-07-29 Something is wrong with the PIT Timer
